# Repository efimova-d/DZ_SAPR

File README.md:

# ДЗ по САПР: протез кисти руки миоэлектрический с обратной связью

**Выполнила:** Ефимова Д.С., группа БМТ2-31М, МГТУ им. Н.Э. Баумана
**Проверил:** Рязанцев П.
**САПР:** KiCad 10

```bash
git clone --recursive https://github.com/efimova-d/DZ_SAPR.git
```

## 1. Библиотека компонентов

- **Состав:** библиотека `GOST_ESKD` содержит 22 символа (УГО по ГОСТ ЕСКД) и 12 посадочных мест.
- **Подключение:** библиотека подключена как git-сабмодуль в `lib/GOST_ESKD`.
- **Пути:** относительные, в `sym-lib-table` и `fp-lib-table` проекта:
  `${KIPRJMOD}/lib/GOST_ESKD/GOST_ESKD.kicad_sym` и `${KIPRJMOD}/lib/GOST_ESKD/GOST_ESKD.pretty`.
- **Размеры УГО** соответствуют ГОСТ 2.728, 2.730, 2.736, 2.743, 2.755 и 2.759.
- **Линии УГО** той же толщины, что линии связи (ГОСТ 2.721).
- **Шрифт** — ГОСТ тип Б, выводы на сетке 2,54 мм.

## 2. Схема электрическая принципиальная

- **Формат:** A3, рамка и основная надпись по ГОСТ 2.104 (форма 1).
- **Обозначение:** БИГЕ.944421.001 Э3, литера «У».
- **Позиционные обозначения** — по ГОСТ 2.710; части многосекционного элемента обозначены через точку: DA2.1 … DA2.5.
- **ОУ DA1, DA2** — по ГОСТ 2.759: поля с обозначениями выводов (+IN, −IN, OUT, RG, REF, +U, −U), знак ▷∞; питание TL074 вынесено в отдельную часть DA2.5.
- **Разъёмы X1–X3** — табличная форма по ГОСТ 2.755 с графами «Конт.» и «Цепь».
- **Шины питания** +5 В, −5 В, +3,3 В и общий провод изображены по ГОСТ 2.702 и ГОСТ 2.721.
- **ERC:** 0 ошибок.

## 3. Классы цепей

| Класс | Цвет | Шаблоны | Цепи |
|---|---|---|---|
| Power | красный | `+5V`, `-5V`, `+3.3V` | шины питания |
| GND | синий | `GND` | общий провод |
| Analog_EMG | голубой | `/EMG_*` | тракт ЭМГ: EMG_P, EMG_N, EMG_AMP, EMG_AC, EMG_RECT, EMG_ENV, EMG_OUT |
| Sensors | оранжевый | `/FSR*`, `/TEMP_DQ` | датчики силы и температуры |
| Control | фиолетовый | `*_CTRL`, `/SERVO_PWM` | управляющие сигналы МК |
| Drive | розовый | `*_DRV` | силовые цепи нагрузок |

## 4. Manufacturer_Part_Number

| Поз. обозначение | Номинал | Кол. | Manufacturer_Part_Number | Manufacturer |
|---|---|---|---|---|
| BK1 | DS18B20 | 1 | DS18B20+ | Analog Devices |
| BP1–BP3 | FSR402 | 3 | 30-81794 | Interlink Electronics |
| BQ1 | Buzzer | 1 | PKLCS1212E4001-R1 | Murata |
| C1, C4 | 1мк | 2 | CL21B105KBFNNNE | Samsung Electro-Mechanics |
| C2 | 0.01мк | 1 | CL21B103KBANNNC | Samsung Electro-Mechanics |
| C3, C5–C8, C10 | 0,82мк | 6 | C0805X824K3RACAUTO | KEMET |
| C9, C11 | 100н | 2 | CL21B104KBCNNNC | Samsung Electro-Mechanics |
| DA1 | AD620 | 1 | AD620ARZ | Analog Devices |
| DA2 | TL074 | 1 | TL074CDR | Texas Instruments |
| DD1 | STM32F3DISCOVERY | 1 | STM32F3DISCOVERY | STMicroelectronics |
| DD2 | FS5106 | 1 | FS5106B | Feetech |
| M1 | QX-4A | 1 | QX-4A | — |
| R1, R7 | 82k | 2 | RC0805FR-0782KL | Yageo |
| R2–R4, R6, R10 | 150k | 5 | RC0805FR-07150KL | Yageo |
| R5 | 10к | 1 | 3266W-1-103LF | Bourns |
| R8 | 200 | 1 | RC0805FR-07200RL | Yageo |
| R9, R14, R15 | 1к | 3 | RC0805FR-071KL | Yageo |
| R11, R12, R16, R17 | 3,3к | 4 | RC0805FR-073K3L | Yageo |
| R13 | 4,7к | 1 | RC0805FR-074K7L | Yageo |
| R18 | 10к | 1 | RC0805FR-0710KL | Yageo |
| VD1, VD2 | 1N4148 | 2 | 1N4148 | onsemi |
| VD3 | 2Д204А | 1 | 2Д204А | — |
| VT1, VT2 | IRLZ34N | 2 | IRLZ34NPBF | Infineon Technologies |
| X1, X3 | разъём 1×3 | 2 | 61300311121 | Würth Elektronik |
| X2 | разъём 1×2 | 1 | 61300211121 | Würth Elektronik |

## 5. Печатная плата (технология «Резонит», DFMA)

**Параметры платы:**
- 2 слоя, FR4 толщиной 1,6 мм, фольга 35 мкм;
- габариты 55,5 × 34,5 мм;
- все компоненты на верхней стороне;
- один полигон GND на всю плату на обоих слоях (общий провод один, без разделения на аналоговую и цифровую землю);
- каждая дорожка одной ширины по всей длине: сигнальные 0,254 мм, питание и GND 0,4 мм (ширина задана в классах цепей Power и GND);
- острых углов нет, повороты дорожек выполнены двумя изломами по 45°, ответвления — под 90°.

Правила завода «Резонит» (уровень «Базовый») записаны в `DZ_SAPR.kicad_dru`. **DRC:** 0 ошибок, 0 неразведённых соединений, 0 несоответствий схеме.

| Параметр | Норма «Резонит» | На плате |
|---|---|---|
| Ширина проводника | ≥ 0,2 мм | 0,254 мм, питание и GND 0,4 мм |
| Зазор | ≥ 0,2 мм | 0,2 мм |
| Металлизированное отверстие | ≥ 0,3 мм | 0,4 мм и более |
| Поясок переходного отверстия | ≥ 0,15 мм | 0,2 мм (отверстия 0,8/0,4 мм), 0,35 мм (1,7/1,0 мм) |
| Поясок монтажной площадки | ≥ 0,2 мм | 0,32–0,40 мм (BK1 — 0,15 мм, уровень «Продвинутый») |
| Медь до края платы | ≥ 0,25 мм | ≥ 0,5 мм |
| Маркировка: шрифт / линия | ≥ 1 мм / ≥ 0,15 мм | 1 мм / 0,15 мм |

**Решения DFMA:**
- односторонний монтаж;
- единый типоразмер пассивных компонентов 0805;
- переходные отверстия 1,0 и 0,4 мм (не меньше нормы завода 0,3 мм);
- разъёмы с шагом 2,54 мм.

## 6. Скрипт ERC, DRC, Gerber, BOM, PDF

`scripts/build.bat` (Windows) и `scripts/build.sh` (Linux / Git Bash) выполняют проверки и выпуск документации. Результаты складываются в папку `output/`:

| Шаг | Результат |
|---|---|
| ERC | `output/erc.rpt` |
| DRC (с проверкой соответствия схеме) | `output/drc.rpt` |
| PDF схемы | `output/DZ_SAPR_schematic.pdf` |
| BOM | `output/DZ_SAPR_bom.csv` |
| Gerber + сверловка | `output/DZ_SAPR_gerbers.zip` |
| 3D-модель | `output/DZ_SAPR.step` |

При ошибках ERC или DRC скрипт останавливается.

## 7. Структура репозитория

```
DZ_SAPR/
├── DZ_SAPR.kicad_pro / .kicad_sch / .kicad_pcb / .kicad_dru
├── sym-lib-table, fp-lib-table
├── lib/GOST_ESKD/          библиотека (git-сабмодуль)
├── scripts/                build.bat, build.sh
├── output/                 результаты скрипта
├── README.md
└── README.pdf
```

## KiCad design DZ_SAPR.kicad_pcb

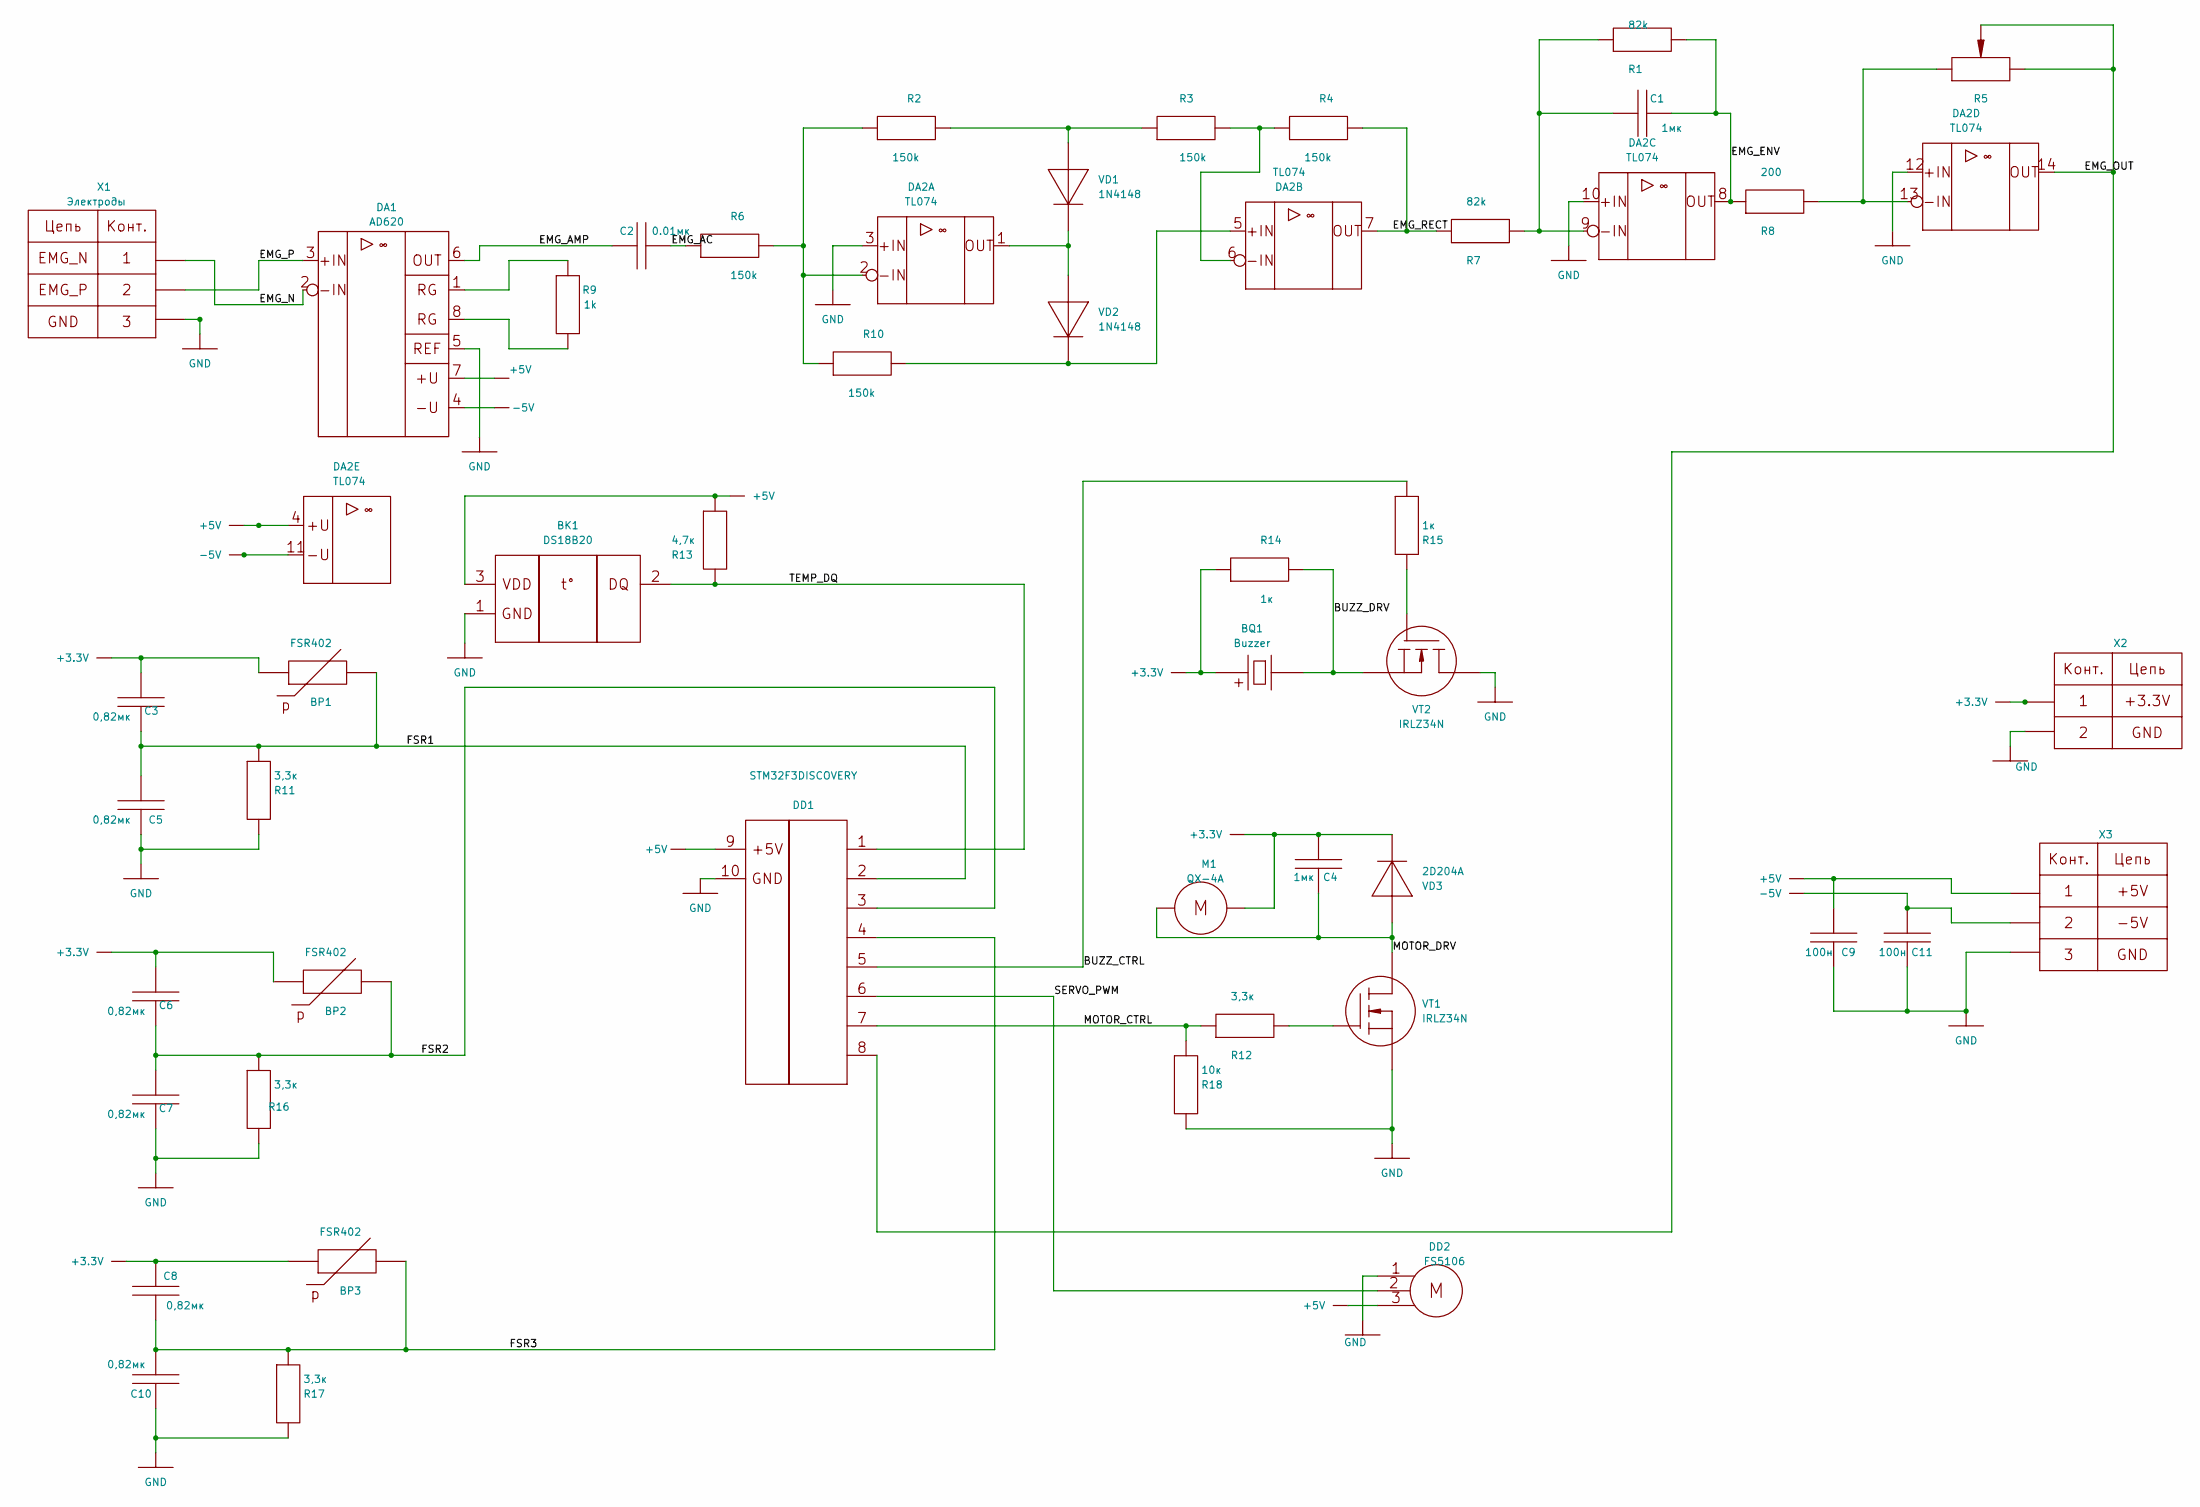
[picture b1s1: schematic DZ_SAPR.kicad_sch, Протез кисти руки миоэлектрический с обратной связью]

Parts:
BK1: DS18B20; TO-92_Inline; Manufacturer_Part_Number DS18B20+
BP1, BP2, BP3: FSR402; PinHeader_1x02_P2.54mm_Vertical; Manufacturer_Part_Number 30-81794
BQ1: Buzzer; Buzzer_Murata_PKLCS1212E; Manufacturer_Part_Number PKLCS1212E4001-R1
C1, C4: 1мк; C_0805_2012Metric; Manufacturer_Part_Number CL21B105KBFNNNE
C2: 0.01мк; C_0805_2012Metric; Manufacturer_Part_Number CL21B103KBANNNC
C3, C5, C6, C7, C8, C10: 0,82мк; C_0805_2012Metric; Manufacturer_Part_Number C0805X824K3RACAUTO
C9, C11: 100н; C_0805_2012Metric; Manufacturer_Part_Number CL21B104KBCNNNC
DA1: AD620; SO-8_3.9x4.9mm_P1.27mm; Manufacturer_Part_Number AD620ARZ
DA2: TL074; SO-14_3.9x8.65mm_P1.27mm; Manufacturer_Part_Number TL074CDR
DD1: STM32F3DISCOVERY; PinHeader_1x10_P2.54mm_Vertical; Manufacturer_Part_Number STM32F3DISCOVERY
DD2: FS5106; PinHeader_1x03_P2.54mm_Vertical; Manufacturer_Part_Number FS5106B
M1: QX-4A; PinHeader_1x02_P2.54mm_Vertical; Manufacturer_Part_Number QX-4A
R1, R7: 82k; R_0805_2012Metric; Manufacturer_Part_Number RC0805FR-0782KL
R2, R3, R4, R6, R10: 150k; R_0805_2012Metric; Manufacturer_Part_Number RC0805FR-07150KL
R5: 10к; Potentiometer_Bourns_3266W_Vertical; Manufacturer_Part_Number 3266W-1-103LF
R8: 200; R_0805_2012Metric; Manufacturer_Part_Number RC0805FR-07200RL
R9: 1k; R_0805_2012Metric; Manufacturer_Part_Number RC0805FR-071KL
R11, R12, R16, R17: 3,3к; R_0805_2012Metric; Manufacturer_Part_Number RC0805FR-073K3L
R13: 4,7к; R_0805_2012Metric; Manufacturer_Part_Number RC0805FR-074K7L
R14, R15: 1к; R_0805_2012Metric; Manufacturer_Part_Number RC0805FR-071KL
R18: 10к; R_0805_2012Metric; Manufacturer_Part_Number RC0805FR-0710KL
VD1, VD2: 1N4148; D_DO-35_SOD27_P7.62mm_Horizontal; Manufacturer_Part_Number 1N4148
VD3: 2D204A; D_DO-35_SOD27_P7.62mm_Horizontal; Manufacturer_Part_Number 2Д204А
VT1, VT2: IRLZ34N; TO-220-3_Vertical; Manufacturer_Part_Number IRLZ34NPBF
X1: Электроды; PinHeader_1x03_P2.54mm_Vertical; Manufacturer_Part_Number 61300311121
X2: Conn_01x02_Pin; PinHeader_1x02_P2.54mm_Vertical; Manufacturer_Part_Number 61300211121
X3: Conn_01x03_Pin; PinHeader_1x03_P2.54mm_Vertical; Manufacturer_Part_Number 61300311121

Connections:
+3.3V: BP1.1, BP2.1, BP3.1, BQ1.1 (+), C3.2, C4.2, C6.2, C8.2, M1.1, R14.1, VD3.1 (K), X2.1 (+3.3V)
+5V: BK1.3 (VDD), C9.2, DA1.7 (+Vs), DA2.4 (V+), DD1.9 (+5V), DD2.3 (+), R13.1, X3.1 (+5V)
-5V: C11.2, DA1.4 (-Vs), DA2.11 (V-), X3.2 (−5V)
/BUZZ_CTRL: DD1.5, R15.1
/BUZZ_DRV: BQ1.2 (-), R14.2, VT2.3 (S)
/EMG_AC: C2.2, R6.1
/EMG_AMP: C2.1, DA1.6 (OUT)
/EMG_ENV: C1.2, DA2.8 (OUT), R1.2, R8.1
/EMG_N: DA1.2 (-IN), X1.1 (EMG_N)
/EMG_OUT: DA2.14 (OUT), DD1.8, R5.2, R5.3
/EMG_P: DA1.3 (+IN), X1.2 (EMG_P)
/EMG_RECT: DA2.7 (OUT), R4.2, R7.1
/FSR1: BP1.2, C3.1, C5.2, DD1.2, R11.1
/FSR2: BP2.2, C6.1, C7.2, DD1.3, R16.1
/FSR3: BP3.2, C8.1, C10.2, DD1.4, R17.1
/MOTOR_CTRL: DD1.7, R12.1, R18.1
/MOTOR_DRV: C4.1, M1.2, VD3.2 (A), VT1.2 (D)
/SERVO_PWM: DD1.6, DD2.2 (S)
/TEMP_DQ: BK1.2 (DQ), DD1.1, R13.2
GND: BK1.1 (GND), C5.1, C7.1, C9.1, C10.1, C11.1, DA1.5 (REF), DA2.3 (+), DA2.10 (+), DA2.12 (+), DD1.10 (GND), DD2.1 (-), R11.2, R16.2, R17.2, R18.2, VT1.3 (S), VT2.2 (D), X1.3 (GND), X2.2 (GND), X3.3 (GND)
unnamed: DA1.1 (RG), R9.1
unnamed: DA1.8 (RG), R9.2
unnamed: DA2.2 (-), R2.1, R6.2, R10.1
unnamed: DA2.5 (+), R10.2, VD2.1 (K)
unnamed: DA2.6 (-), R3.2, R4.1
unnamed: C1.1, DA2.9 (-), R1.1, R7.2
unnamed: DA2.13 (-), R5.1, R8.2
unnamed: R2.2, R3.1, VD1.2 (A)
unnamed: DA2.1 (OUT), VD1.1 (K), VD2.2 (A)
unnamed: R12.2, VT1.1 (G)
unnamed: R15.2, VT2.1 (G)

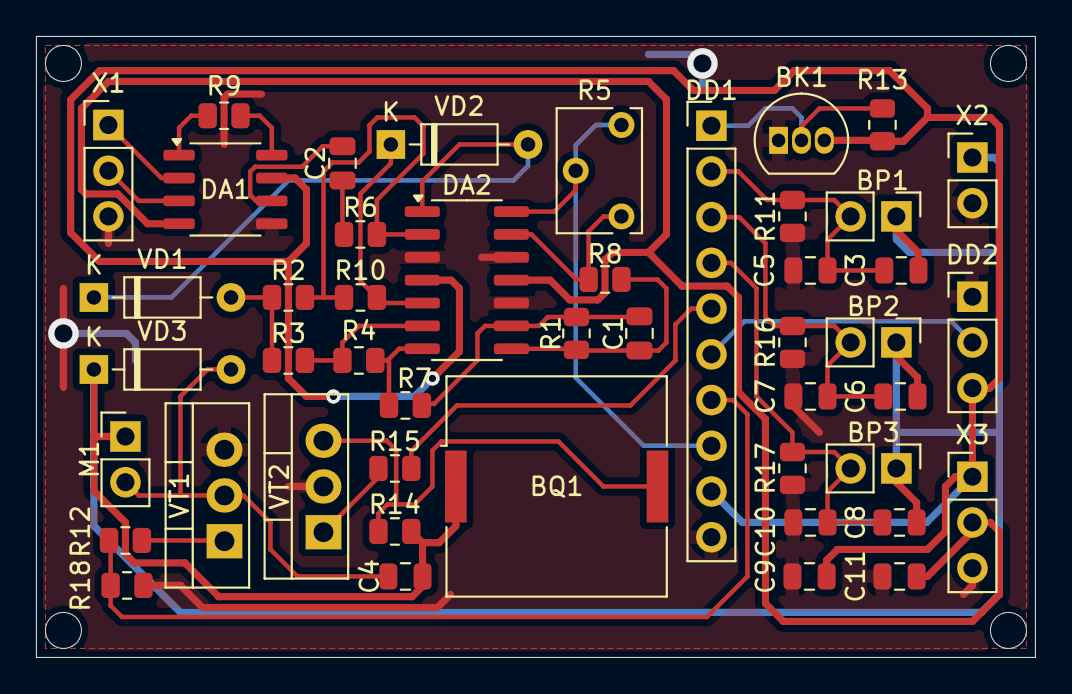
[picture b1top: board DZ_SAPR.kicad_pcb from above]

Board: 2 copper layers, 55.5 x 34.5 mm, 47 parts (0 on the bottom side), 31 nets.
